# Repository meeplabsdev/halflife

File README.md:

# Starbie
|||
|---|---|

Starbie is a tiny (4x4cm) device with two buttons, a gyro+accelerometer and temperature+humidity sensor. Alongside the controls, you can interact with it by physically moving the board.

# What it is
This project was created following the week 1 beginner [tutorial](https://github.com/SharKingStudios/Starbie) for [halflife](https://halflife.hackclub.com/)! I designed the schematic and PCB using [KiCad](https://www.kicad.org/), along with the footprints & symbols provided by the tutorial (for the parts such as the screen, gyro, ...). It can be reprogrammed at will, but comes with some stock firmware to show off the additional sensors connected to the ESP32C3 (such as the accelerometer). Since the microcontroller also has built-in features like 2.4GHz and BLE, I might update the firmware later down the line to take advantage of these features, for example to show which WiFi bands are congested and select the quietest one.

# Hardware
Schematic:

PCB:

|||
|---|---|

# Software
[`firmware/`](starbie/firmware/) contains one Arduino IDE sketch for the XIAO ESP32-C3 that shows the state of the gyro+accelerometer, temperature, humidity, and counts the number of times each button has been pressed. The steps to flash the firmware are as follows:
1. Open the firmware directory in the Arduino IDE and plug the Starbie into the computer via USB.
2. Make sure you have the correct board installed. You can do this by going to `Tools > Board > Boards Manager`, searching `esp32` and installing `esp32 by Espressif Systems`. Then select `Tools > Board > esp32 > XIAO_ESP32C3` and select your board's port under `Tools > Port` (it will probably be the only one).
3. Make sure you have all of the required libraries installed. You can do this by going to `Sketch > Include Library > Manage Libraries` and installing:
    -  Adafruit GFX Library
    -  Adafruit SSD1306
    -  Adafruit MPU6050
    -  DHT sensor library
  If you are prompted to install dependencies, select "Install all".
4. Press the upload button:

# Cost
This is a rough outline of the cost, see [`BOM.md`](bom.md) for more details.

| Part | Cost |
| --- | --- |
| [Keycaps](https://www.alibaba.com/product-detail/Multi-color-1U-M-OA-Profile_1601366568468.html) | $1.08 |
| [Key switches](https://www.alibaba.com/product-detail/GATERON-Grape-Smoothie-Switch-Full-POM_1601822163412.html) | $2.00 |
| [XIAO ESP32C3](https://www.alibaba.com/product-detail/Seeed-Studio-XIAO-ESP32-S3-C3_1601374328247.html) | $5.50 |
| [Screen](https://www.alibaba.com/product-detail/Stock-0-96-Inch-OLED-Module_1600917220368.html) | $1.44 |
| [Temperature & humidity sensor](https://www.alibaba.com/product-detail/Hot-Sell-Original-DHT-11-Digital_62344257902.html) | $0.54 |
| [Gyroscope & accelerometer](https://www.alibaba.com/product-detail/GY-521-MPU-6050-6-Axis_1601943975478.html) | $1.57 |
| [PCB](https://jlcpcb.com) | $4.00 |
| **Total + Shipping** | **$24.54** |

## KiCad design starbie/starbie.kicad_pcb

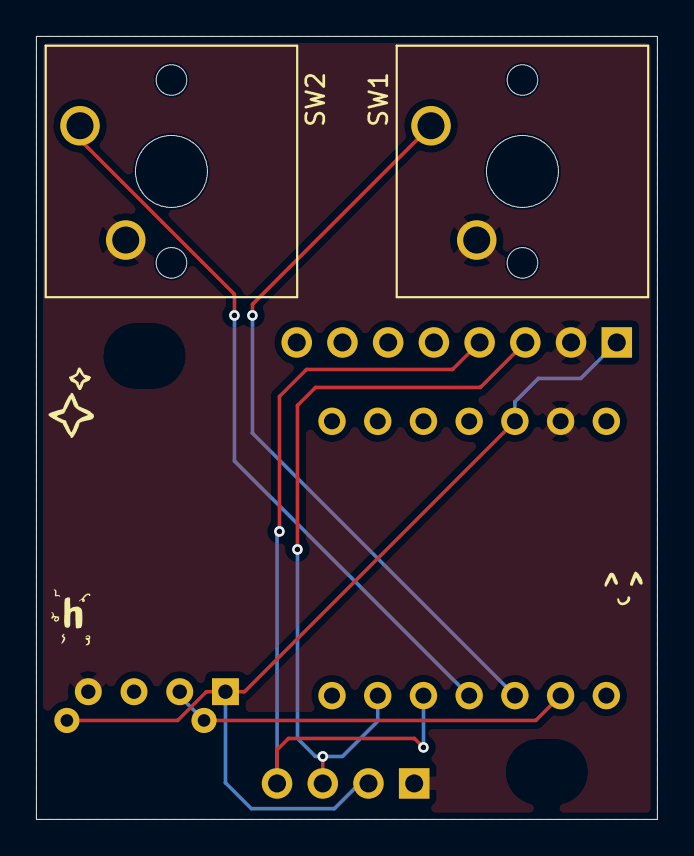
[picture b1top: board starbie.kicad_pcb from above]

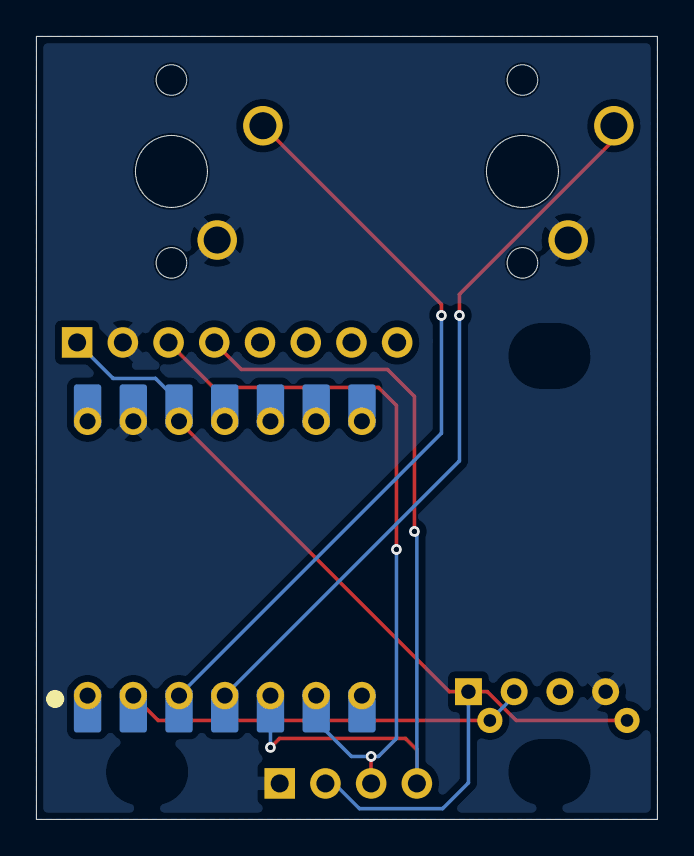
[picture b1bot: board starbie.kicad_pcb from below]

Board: 2 copper layers, 34.5 x 43.5 mm, 7 parts (4 on the bottom side), 7 nets.

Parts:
J1: Conn_01x04_Pin; Display_128x64_096_I2C
J2: Conn_01x08_Pin; PinHeader_1x08_P2.54mm_Vertical
R1: 10k; R_Axial_DIN0204_L3.6mm_D1.6mm_P7.62mm_Horizontal
SW1, SW2: SW_Push; SW_Cherry_MX_1.00u_PCB
U1: XIAO-ESP32-C3-SMD; XIAO-ESP32-C6-DIP
U2: DHT11; Aosong_DHT11_5.5x12.0_P2.54mm

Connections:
+3.3V: J1.2, J2.1, R1.1, U1.12 (3V3_OUT), U2.1 (VDD)
/DHT11_DATA: R1.2, U1.2 (D1), U2.2 (DATA)
/GPIO2: SW1.1, U1.3 (D2)
/GPIO3: SW2.1, U1.4 (D3)
/SCL: J1.3, J2.3, U1.6 (D5)
/SDA: J1.4, J2.4, U1.5 (D4)
GND: J1.1, J2.2, SW1.2, SW2.2, U1.13 (GND), U2.4 (GND)
